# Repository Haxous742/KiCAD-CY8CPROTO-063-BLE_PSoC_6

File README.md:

# CY8CPROTO-063-BLE-PSoC-6
A KiCad project that has the schematic and PCB design for the CY8CPROTO-063-BLE-PSoC-6-BLE-Prototyping-Kit

### Original Image of CY8CPROTO-063-BLE-PSoC-6

### Tools Used

The electronic design and development were done using KiCad, an open-source EDA software. The version used for this project is KiCad 9.0.0.

## Schematic

### Programming Module

### BLE Module

## PCB Layout

### Placement of Components

### Overall PCB Layout

## 3D View

### Top View

### Bottom View

## License

This project is licensed under the MIT License. See the [LICENSE](LICENSE) file for details.

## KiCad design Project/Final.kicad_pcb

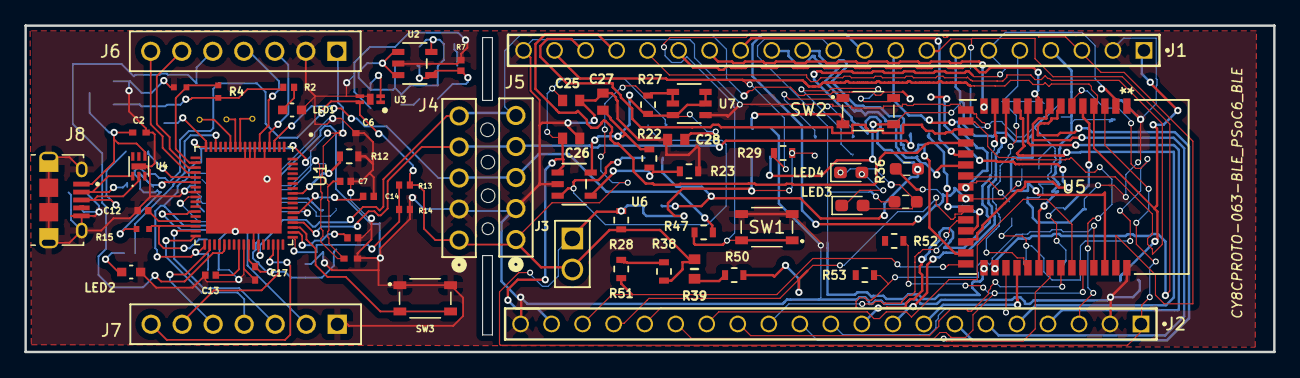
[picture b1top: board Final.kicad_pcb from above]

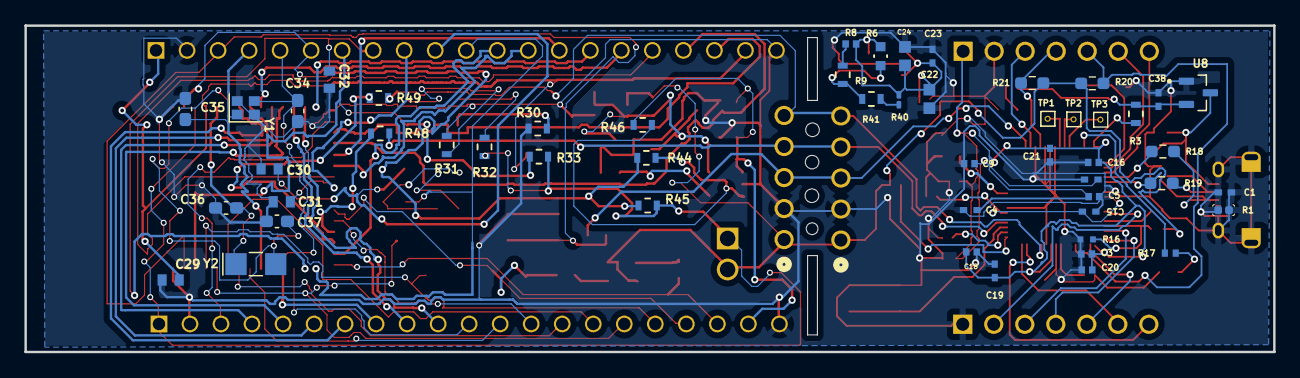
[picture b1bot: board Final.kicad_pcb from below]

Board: 2 copper layers, 102.2 x 26.7 mm, 109 parts (52 on the bottom side), 93 nets.

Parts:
C1: 10nF; G-155_MUR
C2, C4, C6, C8, C10, C15, C17, C19, C21, C23, C38: 0.1uF; CAP_CL05_SAM
C3, C5, C7, C9, C11, C12, C13, C14, C16, C18, C20: 1.0uF; BOM_3
C22, C24: 4.7uF; BOM_4
C25: 0.47uF; CAPC1608X90N
C26, C28: 0.1uF; CAPC1608X90N
C27: 4.7uF; CAPC1608X90N
C29: 10uF; CAPC1608X90N
C30, C31: 0.47nF; CAPC1608X90N
C32: 2.2nF; CAPC1608X90N
C34, C35: 10pF; C_0603_1608Metric_Pad1.08x0.95mm_HandSolder
C36, C37: 22pF; C_0603_1608Metric_Pad1.08x0.95mm_HandSolder
J1, J2: Conn_01x21; SAMTEC_TSW-121-08-G-S
J3: HDR2; CONN_961102-6404-AR_3MM
J4, J5: Conn_01x05; CONN_SD-42375-001_M240_05_MOL
J6, J7: Conn_01x07; J6,J7
J8: 10118194-0001LF; AMPHENOL_10118194-0001LF
LED1: POWER LED; LED_LTST-C191KRKT_LTO
LED2: STATUS LED; LED_LTST-C191KRKT_LTO
LED3: RED LED; LED_0603_1608Metric_Pad1.05x0.95mm_HandSolder
LED4: GREEN LED; LED_0603_1608Metric_Pad1.05x0.95mm_HandSolder
R1: 100K; R1
R2, R17: 2.2K; R2,17
R3, R9, R41: 0ohm; R3,R28,R29,R31,R47,R48,R49,R50,R51,R52,R53
R4, R15: 15K; R4,15
R5, R16: 30K; R5,16
R6: 180K; R6
R7: 57.6K; R7
R8: 383K; R8
R12: 100K; R3,R28,R29,R31,R47,R48,R49,R50,R51,R52,R53
R13, R14: 49.9K; R13,14
R18, R19: 22E; R_0603_1608Metric_Pad0.98x0.95mm_HandSolder
R20, R21: 4.7K; R_0603_1608Metric_Pad0.98x0.95mm_HandSolder
R22: 180K; RES_R0603_ROM
R23: 57.6K; RES_R0603_ROM
R27, R28, R29, R31, R32, R44, R46, R47, R48, R49, R50, R51, R52, R53: 0ohm; RES_R0603_ROM
R30, R33, R45: 10K; RES_R0603_ROM
R36: 470ohm; R_0603_1608Metric_Pad0.98x0.95mm_HandSolder
R37: 330ohm; R_0603_1608Metric_Pad0.98x0.95mm_HandSolder
R38: 4.7k; RES_R0603_ROM
R39: 4.7k; R38,39
R40: 120K; R_0201_0603Metric_Pad0.64x0.40mm_HandSolder
SW1, SW2, SW3: SKRPACE010; SW_SKRPACE010
TP1, TP2, TP3: TestPoint; TestPoint_THTPad_1.0x1.0mm_Drill0.5mm
U1: QFN40P800X800X100-69N
U2: AP7365-WG-7; U2
U3: SIP32408DNP-T1-GE4; SON50P160X120X60-5N-D
U4: 3
U5: CYBLE-416045-02; MOD43_CYBLE-416045-02_INF
U6: AP7365-WG-7; SOT25_DIO
U7: SIP32510DT-T1-GE3; SIP32510DT-T1-GE3_VIS
U8: 2
Y1: 24Mhz; Crystal_SMD_2016-4Pin_2.0x1.6mm
Y2: 32.768KHz; Crystal_SMD_G8-2Pin_3.2x1.5mm_HandSoldering

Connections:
/BLE_Module/I2C_SCL: R39.1, R50.2
/BLE_Module/I2C_SDA: R38.1, R51.2
/BLE_Module/P0_0: C36.2, U5.5 (P0_0), Y2.1
/BLE_Module/P0_1: C37.2, U5.6 (P0_1), Y2.2
/BLE_Module/P0_4: J1.07, R33.1, SW2.3, U5.41 (P0_4)
/BLE_Module/P0_5: J1.06, R37.1, R44.1, R45.2, U5.2 (P0_5)
/BLE_Module/P5_0: J2.16, R52.1, U5.39 (P5_0)
/BLE_Module/P5_1: J2.17, R53.1, U5.40 (P5_1)
/BLE_Module/P5_2: J2.15, U5.38 (P5_2)
/BLE_Module/P5_3: J2.14, U5.37 (P5_3)
/BLE_Module/P5_4: J2.13, U5.25 (P5_4)
/BLE_Module/P5_5: J2.12, U5.36 (P5_5)
/BLE_Module/P5_6: J2.11, U5.32 (P5_6)
/BLE_Module/P6_2: J1.12, U5.28 (P6_2)
/BLE_Module/P6_3: J1.11, R36.2, U5.30 (P6_3)
/BLE_Module/P6_4: J2.18, R50.1, U5.24 (P6_4)
/BLE_Module/P6_5: J2.19, R51.1, U5.29 (P6_5)
/BLE_Module/P6_6: R49.1, U5.27 (P6_6)
/BLE_Module/P6_7: R48.1, U5.26 (P6_7)
/BLE_Module/P6_VDD: C29.2, J1.01, J1.20, R29.1, U5.4 (VDD)
/BLE_Module/P7_1: C30.2, J1.10, R37.2, U5.23 (P7_1)
/BLE_Module/P7_2: C31.2, J1.09, U5.22 (P7_2)
/BLE_Module/P7_7: C32.1, J1.08, U5.31 (P7_7)
/BLE_Module/P9_0: J1.19, U5.17 (P9_0)
/BLE_Module/P9_1: J1.18, U5.18 (P9_1)
/BLE_Module/P9_2: J1.17, U5.21 (P9_2)
/BLE_Module/P9_3: J1.16, U5.9 (P0_3)
/BLE_Module/P9_4: J1.15, U5.14 (P9_4)
/BLE_Module/P9_5: J1.14, U5.19 (P9_5)
/BLE_Module/P9_6: J1.13, U5.20 (P9_6)
/BLE_Module/P10_0: J2.10, U5.13 (P10_0)
/BLE_Module/P10_1: J2.09, U5.12 (P10_1)
/BLE_Module/P10_2: J2.08, U5.33 (P10_2)
/BLE_Module/P10_3: J2.07, U5.7 (P10_3)
/BLE_Module/P10_4: J2.06, U5.8 (P10_4)
/BLE_Module/P10_5: J2.05, U5.11 (P10_5)
/BLE_Module/P10_6: J2.04, U5.10 (P10_6)
/BLE_Module/P12_6: C34.2, J1.05, U5.34 (P12_6), Y1.3
/BLE_Module/P12_7: C35.2, J1.04, U5.35 (P12_7), Y1.1
/BLE_Module/PMIC_EN: R44.2, R46.2, U6.3 (EN)
/BLE_Module/VBACKUP: J2.01, J3.1, R28.2, R29.2, R32.2, R33.2, R45.1, U5.3 (VBACKUP)
/BLE_Module/VCC_3V3: C27.2, C28.1, R22.2, R27.1, U6.5 (OUT), U7.3 (EN), U7.5 (IN), U7.6 (IN)
/BLE_Module/VIN: C25.2, C26.2, J2.20, R46.1, U6.1 (IN)
/BLE_Module/VREF: J2.03, U5.16 (VREF)
/BLE_Module/XRES: J1.03, R47.1, SW1.1, SW1.2, U5.42 (XRES)
/Programming_Module/I2C_SCL: J6.4, R21.1, U1.6 (IND)
/Programming_Module/I2C_SDA: J6.5, R20.1, U1.39 (P12[1])
/Programming_Module/KP_DM: J8.2 (DM), R19.1, U4.1
/Programming_Module/KP_DP: J8.3 (DP), R18.1, U4.2
/Programming_Module/P5LP0_1: J7.7, U1.49 (P0[1])
/Programming_Module/P5LP0_2: J7.6, U1.50 (P0[2])
/Programming_Module/P5LP1_2: SW3.1, SW3.2, U1.54 (P0[5])
/Programming_Module/P5LP1_4: R17.1, U1.15 (P1[4])
/Programming_Module/P5LP3_0: J7.2, U1.29 (P3[0])
/Programming_Module/P5LP3_4: J7.3, U1.33 (P3[4])
/Programming_Module/P5LP3_5: J7.4, U1.34 (P3[5])
/Programming_Module/P5LP3_6: J7.5, U1.36 (P3[6])
/Programming_Module/P5LP12_5: J6.3, U1.4 (P12[5])
/Programming_Module/P5LP_SIO_VREF: R13.2, R14.2, U1.52 (VDDIO)
/Programming_Module/UART_CTS: R12.1, U1.61 (P15[5])
/Programming_Module/UART_RX: J6.7, U1.21 (P12[7])
/Programming_Module/UART_TX: J6.6, U1.20 (P12[6])
/Programming_Module/USB_V_SENSE: R4.2, R5.2, U1.19 (P1[7])
/Programming_Module/VBUS: C38.2, R2.1, R3.1, R4.1, U8.2 (OUT)
/Programming_Module/VBUS_IN: C2.2, J8.1 (VBUS), U4.6, U8.3 (IN)
/Programming_Module/VOUT: C22.1, C23.1, C24.1, R6.1, R8.1, R40.1, U2.1 (IN), U2.3 (EN), U2.5 (OUT), U3.1 (IN), U3.3 (EN)
/Programming_Module/VTARG_MEAS: R15.2, R16.2, U1.32 (P3[3])
GND: C1.1, C1.2, C2.1, C3.2, C4.2, C5.2, C6.2, C7.2, C8.2, C9.2, C10.2, C11.2, C12.2, C13.2, C14.2, C15.2, C16.2, C17.2, C18.2, C19.2, C20.2, C21.2, C22.2, C23.2, C24.2, C25.1, C26.1, C27.1, C28.2, C29.1, C30.1, C31.1, C32.2, C34.1, C35.1, C36.1, C37.1, C38.1, J1.02, J1.21, J2.02, J2.21, J4.2, J5.2, J6.2, J7.1, J8.5 (GND), J8.SH1 (S1), J8.SH2 (S2), J8.SH3 (S3), J8.SH4 (S4), J8.SH5 (S5), J8.SH6 (S6), LED1.1 (K), LED2.1 (K), R1.1, R1.2, R5.1, R7.1, R12.2, R14.1, R16.1, R23.2, R30.1, R31.1, SW1.3, SW1.4, SW3.3, SW3.4, U1.5 (VSSB), U1.7 (VBOOST), U1.8 (VBAT), U1.9 (VSSD), U1.25 (VSSD), U1.43 (VSSA), U1.45 (VSSD), U1.58 (VSSD), U1.H (EPAD), U2.2 (GND), U3.2 (GND), U3.H (PAD), U4.7, U5.1 (GND), U5.15 (GND), U5.43 (GND), U6.2 (GND), U7.4 (GND), U8.1 (GND), Y1.2, Y1.4
unnamed: LED1.2 (A), R2.2
unnamed: LED2.2 (A), R17.2
unnamed: LED3.2 (A), LED4.1 (K), R36.1
unnamed: R8.2, R9.2
unnamed: R30.2, SW2.4
unnamed: R31.2, SW2.2
unnamed: R32.1, SW2.1
unnamed: R40.2, R41.2
unnamed: C11.1, U1.53 (P0[4])
unnamed: TP2.1, U1.11 (P1[0])
unnamed: TP3.1, U1.12 (P1[1])
unnamed: C12.1, U1.31 (P3[2])
unnamed: R18.2, U1.22 (P15[6]D+)
unnamed: R19.2, U1.23 (P15[7]D-)
unnamed: C13.1, U1.42 (VCCA)
unnamed: TP1.1, U1.10 (XRES)
unnamed: R6.2, R7.2, R9.1, R41.1, U2.4 (ADJ)
unnamed: R22.1, R23.1, U6.4 (ADJ)
P5LP_VCCD: C14.1, C15.1, U1.26 (VCCD), U1.57 (VCCD)
P5LP_VDD: C3.1, C4.1, C5.1, C6.1, C7.1, C8.1, C9.1, C10.1, C16.1, C17.1, C18.1, C19.1, C20.1, C21.1, J6.1, R3.2, U1.17 (VDDIO1), U1.35 (VDDIO3), U1.44 (VDDA)
RESET: J4.3, J5.3, R47.2, U1.3 (P12[4])
SWDCLK: J4.4, J5.4, R48.2, U1.55 (P0[6])
SWDIO: J4.5, J5.5, R49.2, U1.46 (P12[2])
VDD: LED3.1 (K), LED4.2 (A)
VTARG: J3.2, J4.1, J5.1, R13.1, R15.1, R20.2, R21.2, R27.2, R28.1, R38.2, R39.2, U3.4 (OUT), U7.1 (OUT), U7.2 (OUT)

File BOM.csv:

"Reference","Value","Footprint","Datasheet","Qty","DNP"
"C1","10nF","A_Library:G-155_MUR","~","1",""
"C2,C4,C6,C8,C10,C15,C17,C19,C21,C23,C26,C28,C38","0.1uF","A_Library:CAP_CL05_SAM,Library:CAPC1608X90N","~","13",""
"C3,C5,C7,C9,C11,C12,C13,C14,C16,C18,C20","1.0uF","A_Library:BOM_3","~","11",""
"C22,C24,C27","4.7uF","A_Library:BOM_4,Library:CAPC1608X90N","~","3",""
"C25","0.47uF","Library:CAPC1608X90N","~","1",""
"C29","10uF","Library:CAPC1608X90N","~","1",""
"C30,C31","0.47nF","Library:CAPC1608X90N","~","2",""
"C32","2.2nF","Library:CAPC1608X90N","~","1",""
"C34,C35","10pF","Capacitor_SMD:C_0603_1608Metric_Pad1.08x0.95mm_HandSolder","~","2",""
"C36,C37","22pF","Capacitor_SMD:C_0603_1608Metric_Pad1.08x0.95mm_HandSolder","~","2",""
"J1,J2","Conn_01x21","A_Library:SAMTEC_TSW-121-08-G-S","~","2",""
"J3","HDR2","A_Library:CONN_961102-6404-AR_3MM","961102-6404-AR","1",""
"J4,J5","Conn_01x05","A_Library:CONN_SD-42375-001_M240_05_MOL","~","2",""
"J6,J7","Conn_01x07","A_Library:J6,J7","~","2",""
"J8","10118194-0001LF","A_Library:AMPHENOL_10118194-0001LF","https://www.amphenol-cs.com/micro-usb-101181940001lf.html","1",""
"LED1","POWER LED","A_Library:LED_LTST-C191KRKT_LTO","~","1",""
"LED2","STATUS LED","A_Library:LED_LTST-C191KRKT_LTO","~","1",""
"LED3","RED LED","LED_SMD:LED_0603_1608Metric_Pad1.05x0.95mm_HandSolder","~","1",""
"LED4","GREEN LED","LED_SMD:LED_0603_1608Metric_Pad1.05x0.95mm_HandSolder","~","1",""
"R1,R12","100K","A_Library:R1,A_Library:R3,R28,R29,R31,R47,R48,R49,R50,R51,R52,R53","~","2",""
"R2,R17","2.2K","A_Library:R2,17","~","2",""
"R3,R9,R27,R28,R29,R31,R32,R41,R44,R46,R47,R48,R49,R50,R51,R52,R53","0ohm","A_Library:R3,R28,R29,R31,R47,R48,R49,R50,R51,R52,R53,Library:RES_R0603_ROM","~","17",""
"R4,R15","15K","A_Library:R4,15","~","2",""
"R5,R16","30K","A_Library:R5,16","~","2",""
"R6,R22","180K","A_Library:R6,Library:RES_R0603_ROM","~","2",""
"R7,R23","57.6K","A_Library:R7,Library:RES_R0603_ROM","~","2",""
"R8","383K","A_Library:R8","~","1",""
"R13,R14","49.9K","A_Library:R13,14","~","2",""
"R18,R19","22E","Resistor_SMD:R_0603_1608Metric_Pad0.98x0.95mm_HandSolder","~","2",""
"R20,R21","4.7K","Resistor_SMD:R_0603_1608Metric_Pad0.98x0.95mm_HandSolder","~","2",""
"R30,R33,R45","10K","Library:RES_R0603_ROM","~","3",""
"R36","470ohm","Resistor_SMD:R_0603_1608Metric_Pad0.98x0.95mm_HandSolder","~","1",""
"R37","330ohm","Resistor_SMD:R_0603_1608Metric_Pad0.98x0.95mm_HandSolder","~","1",""
"R38,R39","4.7k","Library:R38,39,Library:RES_R0603_ROM","~","2",""
"R40","120K","Resistor_SMD:R_0201_0603Metric_Pad0.64x0.40mm_HandSolder","~","1",""
"SW1,SW2,SW3","SKRPACE010","Library:SW_SKRPACE010","","3",""
"TP1,TP2,TP3","TestPoint","TestPoint:TestPoint_THTPad_1.0x1.0mm_Drill0.5mm","~","3",""
"U1,U4,U8","~","Library:2,Library:3,Library:QFN40P800X800X100-69N","","3",""
"U2,U6","AP7365-WG-7","A_Library:SOT25_DIO","AP7365-WG-7","2",""
"U3","SIP32408DNP-T1-GE4","Library:SON50P160X120X60-5N-D","http://www.vishay.com/docs/63717/sip32408.pdf","1",""
"U5","CYBLE-416045-02","A_Library:MOD43_CYBLE-416045-02_INF","CYBLE-416045-02","1",""
"U7","SIP32510DT-T1-GE3","A_Library:SIP32510DT-T1-GE3_VIS","SIP32510DT-T1-GE3","1",""
"Y1","24Mhz","Crystal:Crystal_SMD_2016-4Pin_2.0x1.6mm","~","1",""
"Y2","32.768KHz","Crystal:Crystal_SMD_G8-2Pin_3.2x1.5mm_HandSoldering","~","1",""

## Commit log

2025-06-14 Initial
2025-06-14 Added Files
2025-06-14 Final
2025-06-14 ReadMe
